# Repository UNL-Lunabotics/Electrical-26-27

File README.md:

# Electrical-26-27
Electrical's pcb projects and documentation.

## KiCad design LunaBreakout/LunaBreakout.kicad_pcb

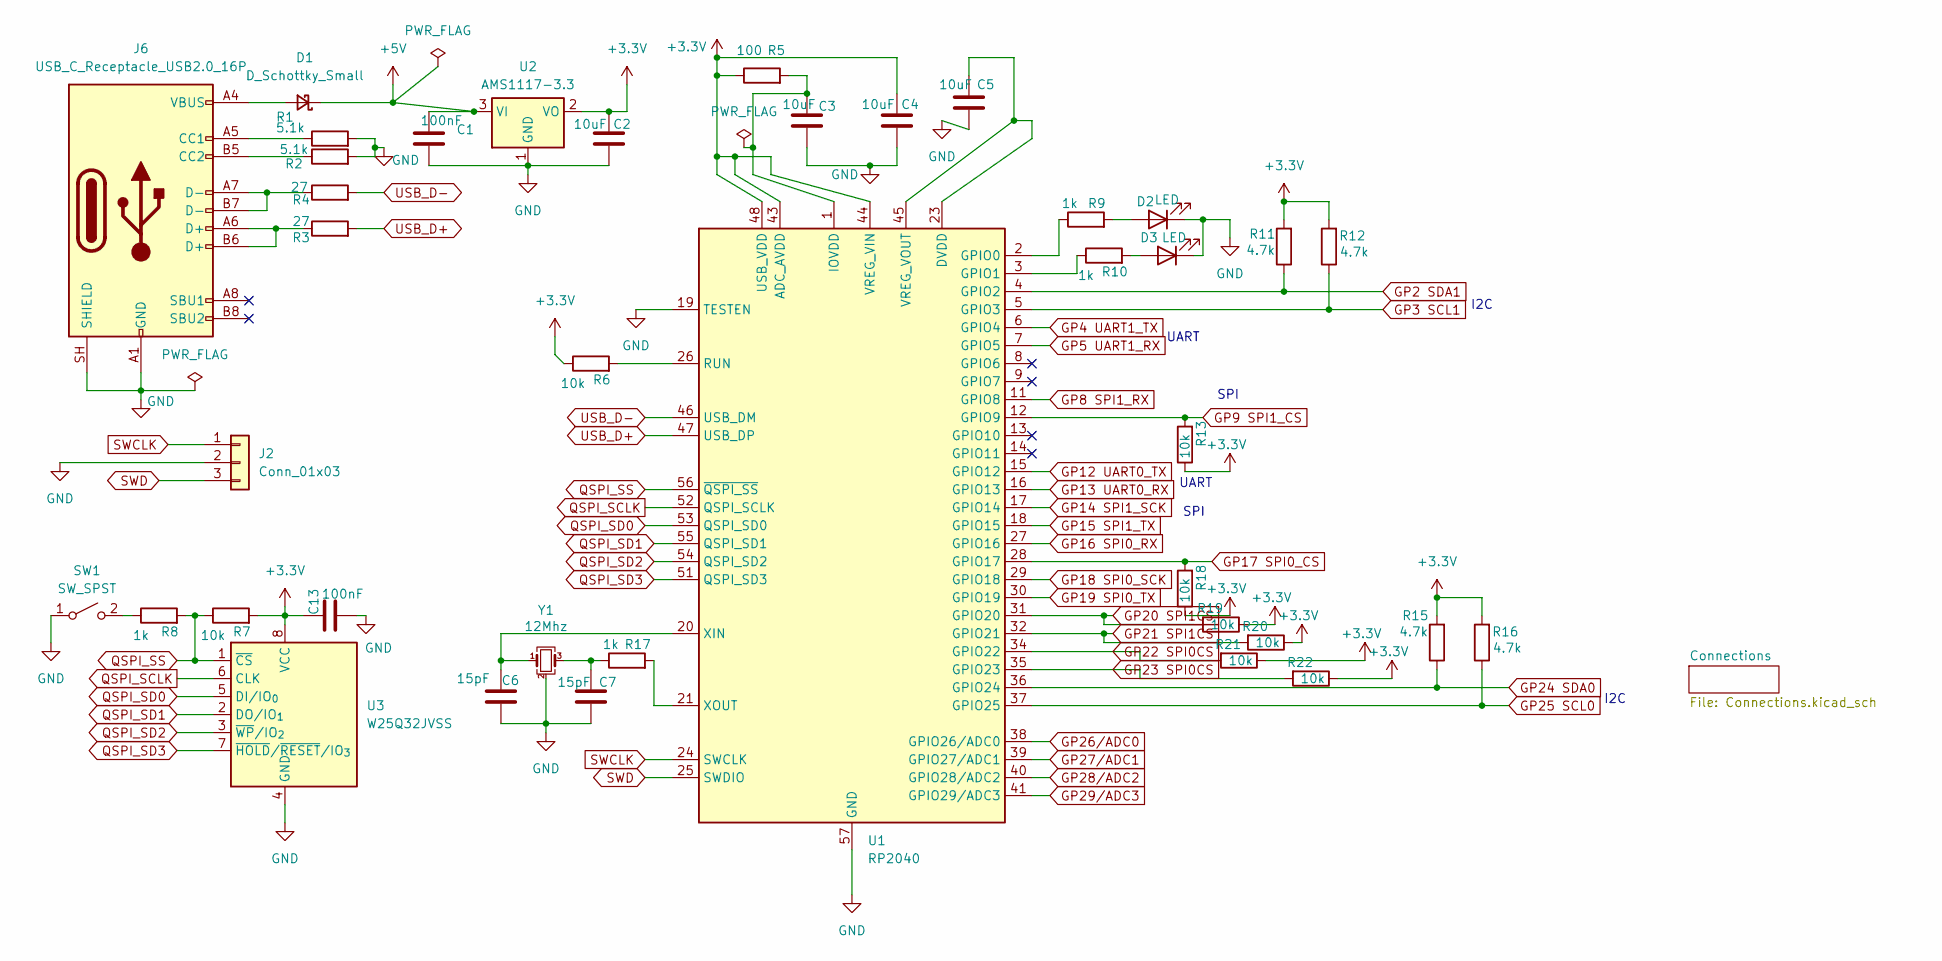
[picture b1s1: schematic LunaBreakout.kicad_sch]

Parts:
C1, C13: 100nF; C_0805_2012Metric
C2, C3, C4, C5: 10uF; C_0805_2012Metric
C6, C7: 15pF; C_0805_2012Metric
D1: D_Schottky_Small; D_SMA
D2, D3: LED; LED_0805_2012Metric
J2: Conn_01x03; JST_XH_B3B-XH-A_1x03_P2.50mm_Vertical
J6: USB_C_Receptacle_USB2.0_16P; USB_C_Receptacle_HRO_TYPE-C-31-M-12
R1, R2: 5.1k; R_0805_2012Metric
R3, R4: 27; R_0805_2012Metric
R5: 100; R_0805_2012Metric
R6, R7, R13, R18, R19, R20, R21, R22: 10k; R_0805_2012Metric
R8, R9, R10, R17: 1k; R_0805_2012Metric
R11, R12, R15, R16: 4.7k; R_0805_2012Metric
SW1: SW_SPST; SW_SPST_CK_RS282G05A3
U1: RP2040; QFN-56-1EP_7x7mm_P0.4mm_EP3.2x3.2mm
U2: AMS1117-3.3; SOT-223-3_TabPin2
U3: W25Q32JVSS; WSON-8-1EP_4x4mm_P0.8mm_EP2.2x3mm
Y1: 12Mhz; Crystal_SMD_SeikoEpson_FA238V-4Pin_3.2x2.5mm

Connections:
+3.3V: C2.1, C4.1, C13.1, R5.1, R6.1, R7.2, R11.2, R12.2, R13.1, R15.2, R16.2, R18.1, R19.1, R20.1, R21.1, R22.1, U1.43 (ADC_AVDD), U1.44 (VREG_VIN), U1.48 (USB_VDD), U2.2 (VO), U3.8 (VCC); also elsewhere on the board
+5V: C1.1, D1.1 (K), U2.3 (VI)
GND: C1.2, C2.2, C3.2, C4.2, C5.2, C6.2, C7.2, C13.2, D2.1 (K), D3.1 (K), J2.2, J6.A1 (GND), J6.A12 (GND), J6.B1 (GND), J6.B12 (GND), J6.SH (SHIELD), R1.2, R2.2, SW1.1 (A), U1.19 (TESTEN), U1.57 (GND), U2.1 (GND), U3.4 (GND), U3.9, Y1.2 (G), Y1.4 (G); also elsewhere on the board
GP2 SDA1: R11.1, U1.4 (GPIO2); also elsewhere on the board
GP3 SCL1: R12.1, U1.5 (GPIO3); also elsewhere on the board
GP4 UART1_TX: U1.6 (GPIO4); also elsewhere on the board
GP5 UART1_RX: U1.7 (GPIO5); also elsewhere on the board
GP8 SPI1_RX: U1.11 (GPIO8); also elsewhere on the board
GP9 SPI1_CS: R13.2, U1.12 (GPIO9); also elsewhere on the board
GP12 UART0_TX: U1.15 (GPIO12); also elsewhere on the board
GP13 UART0_RX: U1.16 (GPIO13); also elsewhere on the board
GP14 SPI1_SCK: U1.17 (GPIO14); also elsewhere on the board
GP15 SPI1_TX: U1.18 (GPIO15); also elsewhere on the board
GP16 SPI0_RX: U1.27 (GPIO16); also elsewhere on the board
GP17 SPI0_CS: R18.2, U1.28 (GPIO17); also elsewhere on the board
GP18 SPI0_SCK: U1.29 (GPIO18); also elsewhere on the board
GP19 SPI0_TX: U1.30 (GPIO19); also elsewhere on the board
GP20 SPI1CS: R19.2, U1.31 (GPIO20); also elsewhere on the board
GP21 SPI1CS: R20.2, U1.32 (GPIO21); also elsewhere on the board
GP22 SPI0CS: R21.2, U1.34 (GPIO22); also elsewhere on the board
GP23 SPI0CS: R22.2, U1.35 (GPIO23); also elsewhere on the board
GP24 SDA0: R15.1, U1.36 (GPIO24); also elsewhere on the board
GP25 SCL0: R16.1, U1.37 (GPIO25); also elsewhere on the board
GP26/ADC0: U1.38 (GPIO26/ADC0); also elsewhere on the board
GP27/ADC1: U1.39 (GPIO27/ADC1); also elsewhere on the board
GP28/ADC2: U1.40 (GPIO28/ADC2); also elsewhere on the board
GP29/ADC3: U1.41 (GPIO29/ADC3); also elsewhere on the board
unnamed: C3.1, R5.2, U1.1 (IOVDD), U1.10 (IOVDD), U1.22 (IOVDD), U1.33 (IOVDD), U1.42 (IOVDD), U1.49 (IOVDD)
unnamed: C7.1, R17.1, Y1.3
unnamed: D1.2 (A), J6.A4 (VBUS), J6.A9 (VBUS), J6.B4 (VBUS), J6.B9 (VBUS)
unnamed: D2.2 (A), R9.2
unnamed: D3.2 (A), R10.2
unnamed: J6.A5 (CC1), R1.1
unnamed: J6.B5 (CC2), R2.1
unnamed: J6.A6 (D+), J6.B6 (D+), R3.1
unnamed: J6.A7 (D-), J6.B7 (D-), R4.1
unnamed: R8.1, SW1.2 (B)
unnamed: R9.1, U1.2 (GPIO0)
unnamed: R10.1, U1.3 (GPIO1)
unnamed: R6.2, U1.26 (RUN)
unnamed: C5.1, U1.23 (DVDD), U1.45 (VREG_VOUT), U1.50 (DVDD)
unnamed: C6.1, U1.20 (XIN), Y1.1
unnamed: R17.2, U1.21 (XOUT)
QSPI_SCLK: U1.52 (QSPI_SCLK), U3.6 (CLK)
QSPI_SD0: U1.53 (QSPI_SD0), U3.5 (DI/IO_{0})
QSPI_SD1: U1.55 (QSPI_SD1), U3.2 (DO/IO_{1})
QSPI_SD2: U1.54 (QSPI_SD2), U3.3 (~WP/IO_{2})
QSPI_SD3: U1.51 (QSPI_SD3), U3.7 (~HOLD/~RESET/IO_{3})
QSPI_SS: R7.1, R8.2, U1.56 (~QSPI_SS), U3.1 (~CS)
SWCLK: J2.1, U1.24 (SWCLK)
SWD: J2.3, U1.25 (SWDIO)
USB_D+: R3.2, U1.47 (USB_DP)
USB_D-: R4.2, U1.46 (USB_DM)

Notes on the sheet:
I2C
SPI
UART

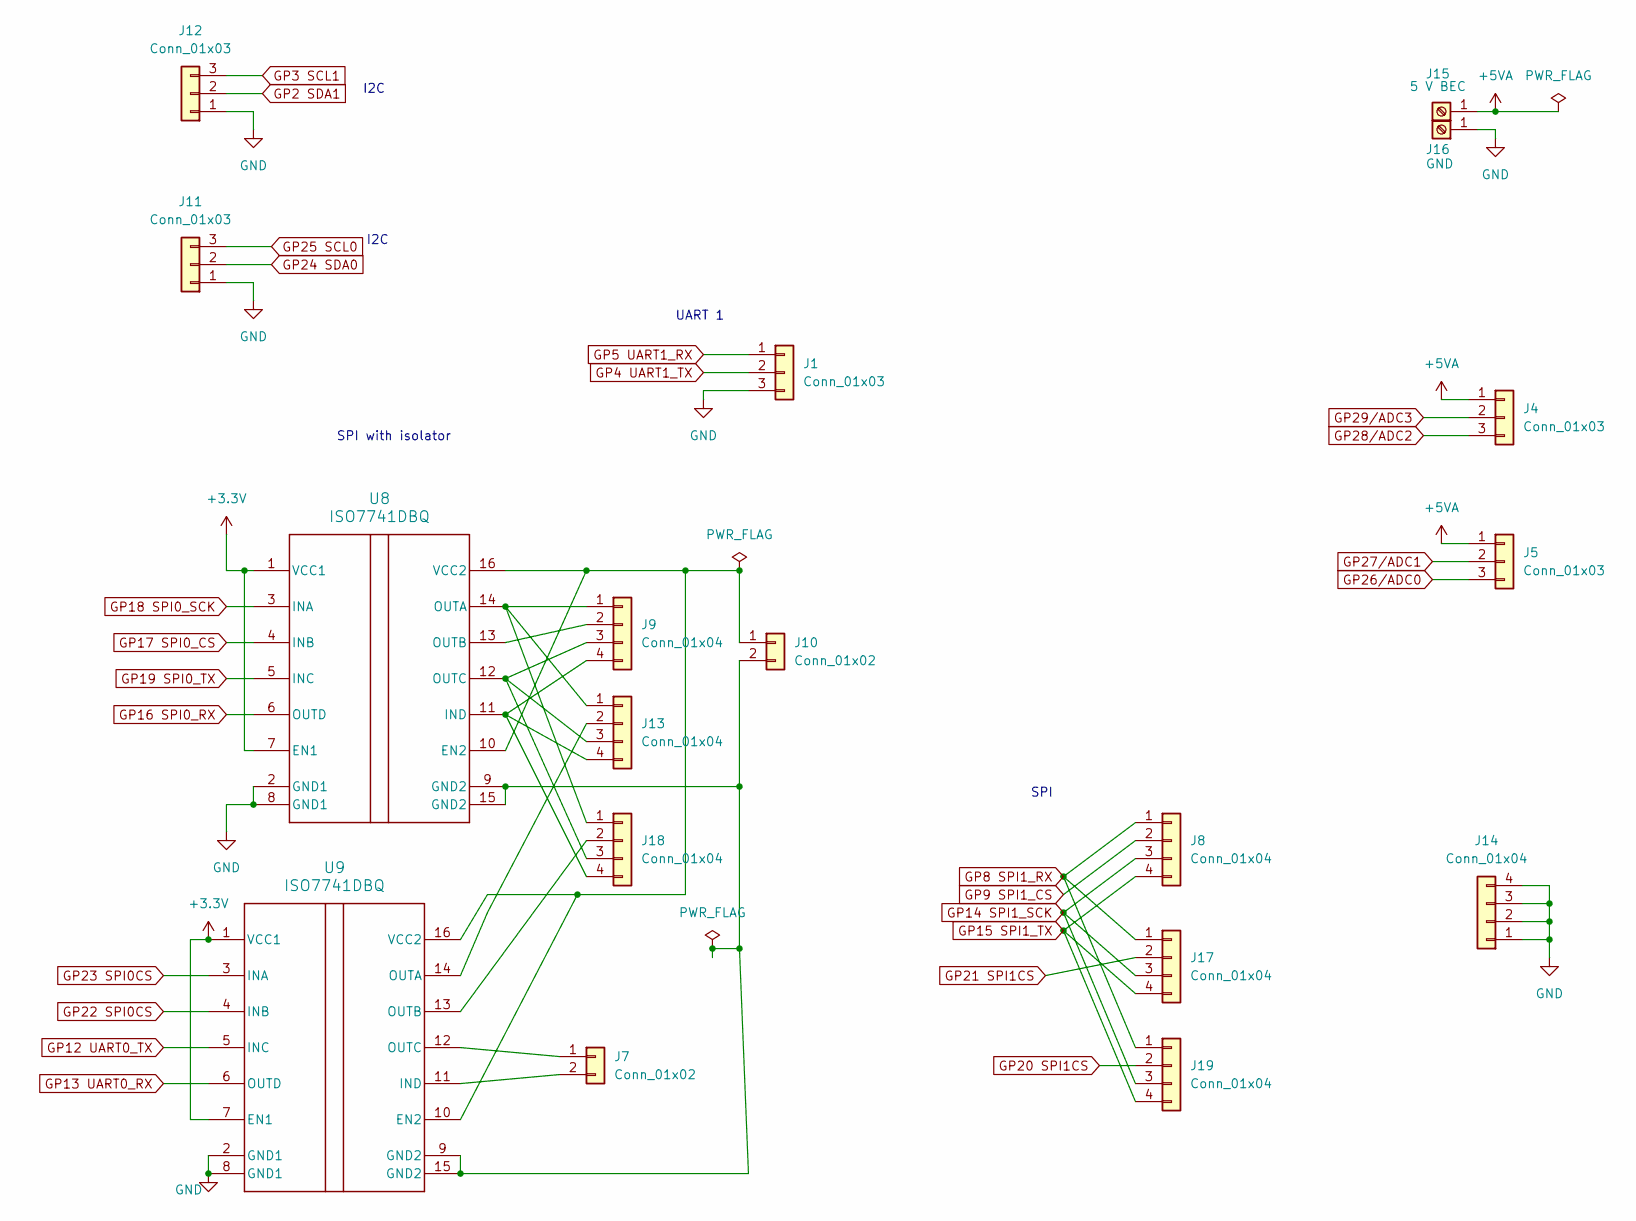
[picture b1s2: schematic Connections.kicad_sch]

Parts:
J1, J4, J5, J11, J12: Conn_01x03; JST_XH_B3B-XH-A_1x03_P2.50mm_Vertical
J7, J10: Conn_01x02; JST_XH_B2B-XH-A_1x02_P2.50mm_Vertical
J8, J9, J13, J14, J17, J18, J19: Conn_01x04; JST_XH_B4B-XH-A_1x04_P2.50mm_Vertical
J15: 5 V BEC; Amphenol_Anytek_AMT0440008DB0000G
J16: GND; Amphenol_Anytek_AMT0440008DB0000G
U8, U9: ISO7741DBQ; DBQ0016A_N

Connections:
+3.3V: U8.1 (VCC1), U8.7 (EN1), U9.1 (VCC1), U9.7 (EN1); also elsewhere on the board
+5VA: J4.1, J5.1, J15.1 (Pin_1_1)
GND: J1.3, J11.1, J12.1, J14.1, J14.2, J14.3, J14.4, J16.1 (Pin_1_1), U8.2 (GND1), U8.8 (GND1), U9.2 (GND1), U9.8 (GND1); also elsewhere on the board
GP2 SDA1: J12.2; also elsewhere on the board
GP3 SCL1: J12.3; also elsewhere on the board
GP4 UART1_TX: J1.2; also elsewhere on the board
GP5 UART1_RX: J1.1; also elsewhere on the board
GP8 SPI1_RX: J8.1, J17.1, J19.1; also elsewhere on the board
GP9 SPI1_CS: J8.2; also elsewhere on the board
GP12 UART0_TX: U9.5 (INC); also elsewhere on the board
GP13 UART0_RX: U9.6 (OUTD); also elsewhere on the board
GP14 SPI1_SCK: J8.3, J17.3, J19.3; also elsewhere on the board
GP15 SPI1_TX: J8.4, J17.4, J19.4; also elsewhere on the board
GP16 SPI0_RX: U8.6 (OUTD); also elsewhere on the board
GP17 SPI0_CS: U8.4 (INB); also elsewhere on the board
GP18 SPI0_SCK: U8.3 (INA); also elsewhere on the board
GP19 SPI0_TX: U8.5 (INC); also elsewhere on the board
GP20 SPI1CS: J19.2; also elsewhere on the board
GP21 SPI1CS: J17.2; also elsewhere on the board
GP22 SPI0CS: U9.4 (INB); also elsewhere on the board
GP23 SPI0CS: U9.3 (INA); also elsewhere on the board
GP24 SDA0: J11.2; also elsewhere on the board
GP25 SCL0: J11.3; also elsewhere on the board
GP26/ADC0: J5.3; also elsewhere on the board
GP27/ADC1: J5.2; also elsewhere on the board
GP28/ADC2: J4.3; also elsewhere on the board
GP29/ADC3: J4.2; also elsewhere on the board
unnamed: J7.1, U9.12 (OUTC)
unnamed: J7.2, U9.11 (IND)
unnamed: J9.2, U8.13 (OUTB)
unnamed: J10.1, U8.10 (EN2), U8.16 (VCC2), U9.10 (EN2), U9.16 (VCC2)
unnamed: J10.2, U8.9 (GND2), U8.15 (GND2), U9.9 (GND2), U9.15 (GND2)
unnamed: J9.1, J13.1, J18.1, U8.14 (OUTA)
unnamed: J13.2, U9.14 (OUTA)
unnamed: J9.3, J13.3, J18.3, U8.12 (OUTC)
unnamed: J9.4, J13.4, J18.4, U8.11 (IND)
unnamed: J18.2, U9.13 (OUTB)

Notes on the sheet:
SPI
SPI with isolator
I2C
UART 1

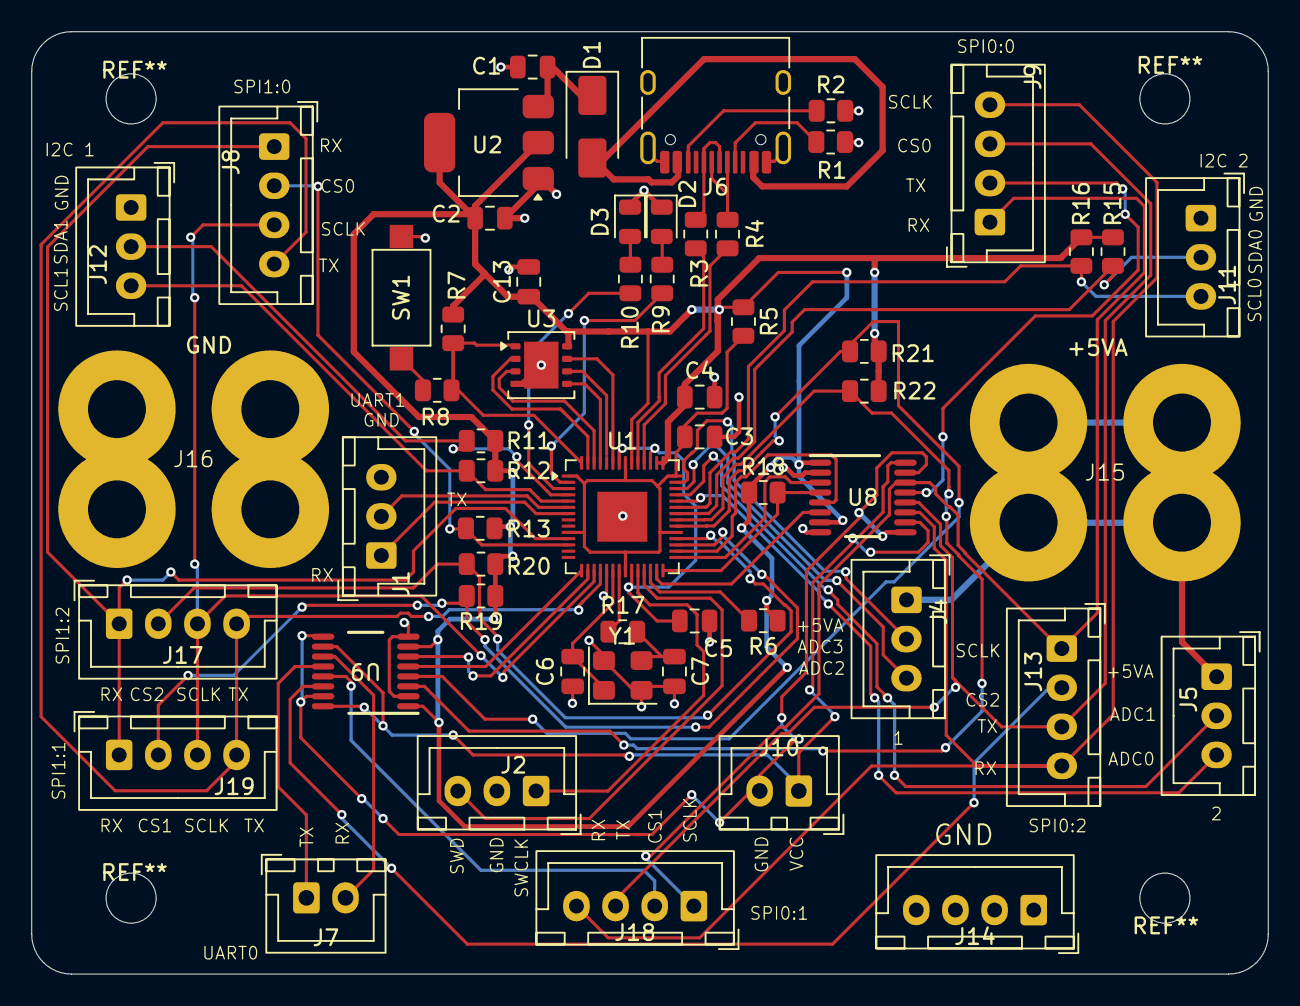
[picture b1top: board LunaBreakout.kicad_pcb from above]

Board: 2 copper layers, 79.0 x 60.2 mm, 57 parts (0 on the bottom side), 64 nets.

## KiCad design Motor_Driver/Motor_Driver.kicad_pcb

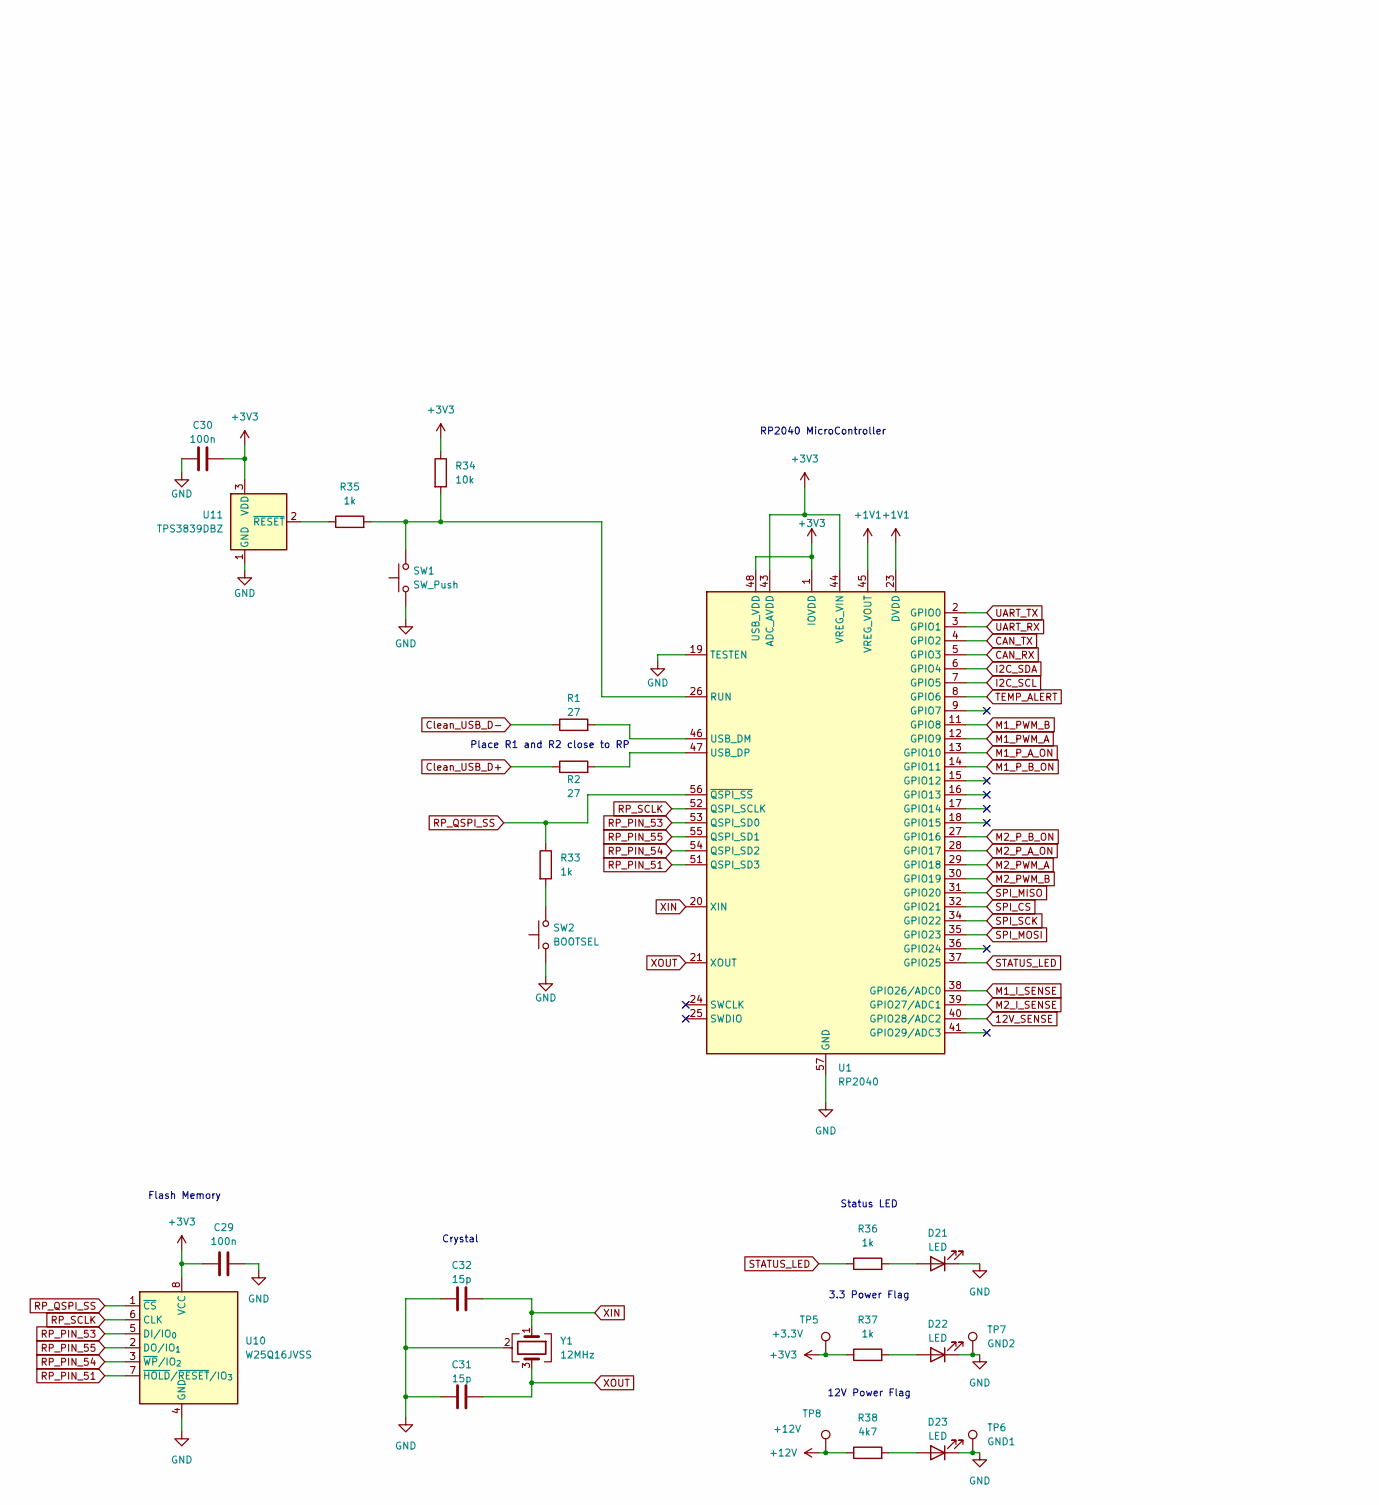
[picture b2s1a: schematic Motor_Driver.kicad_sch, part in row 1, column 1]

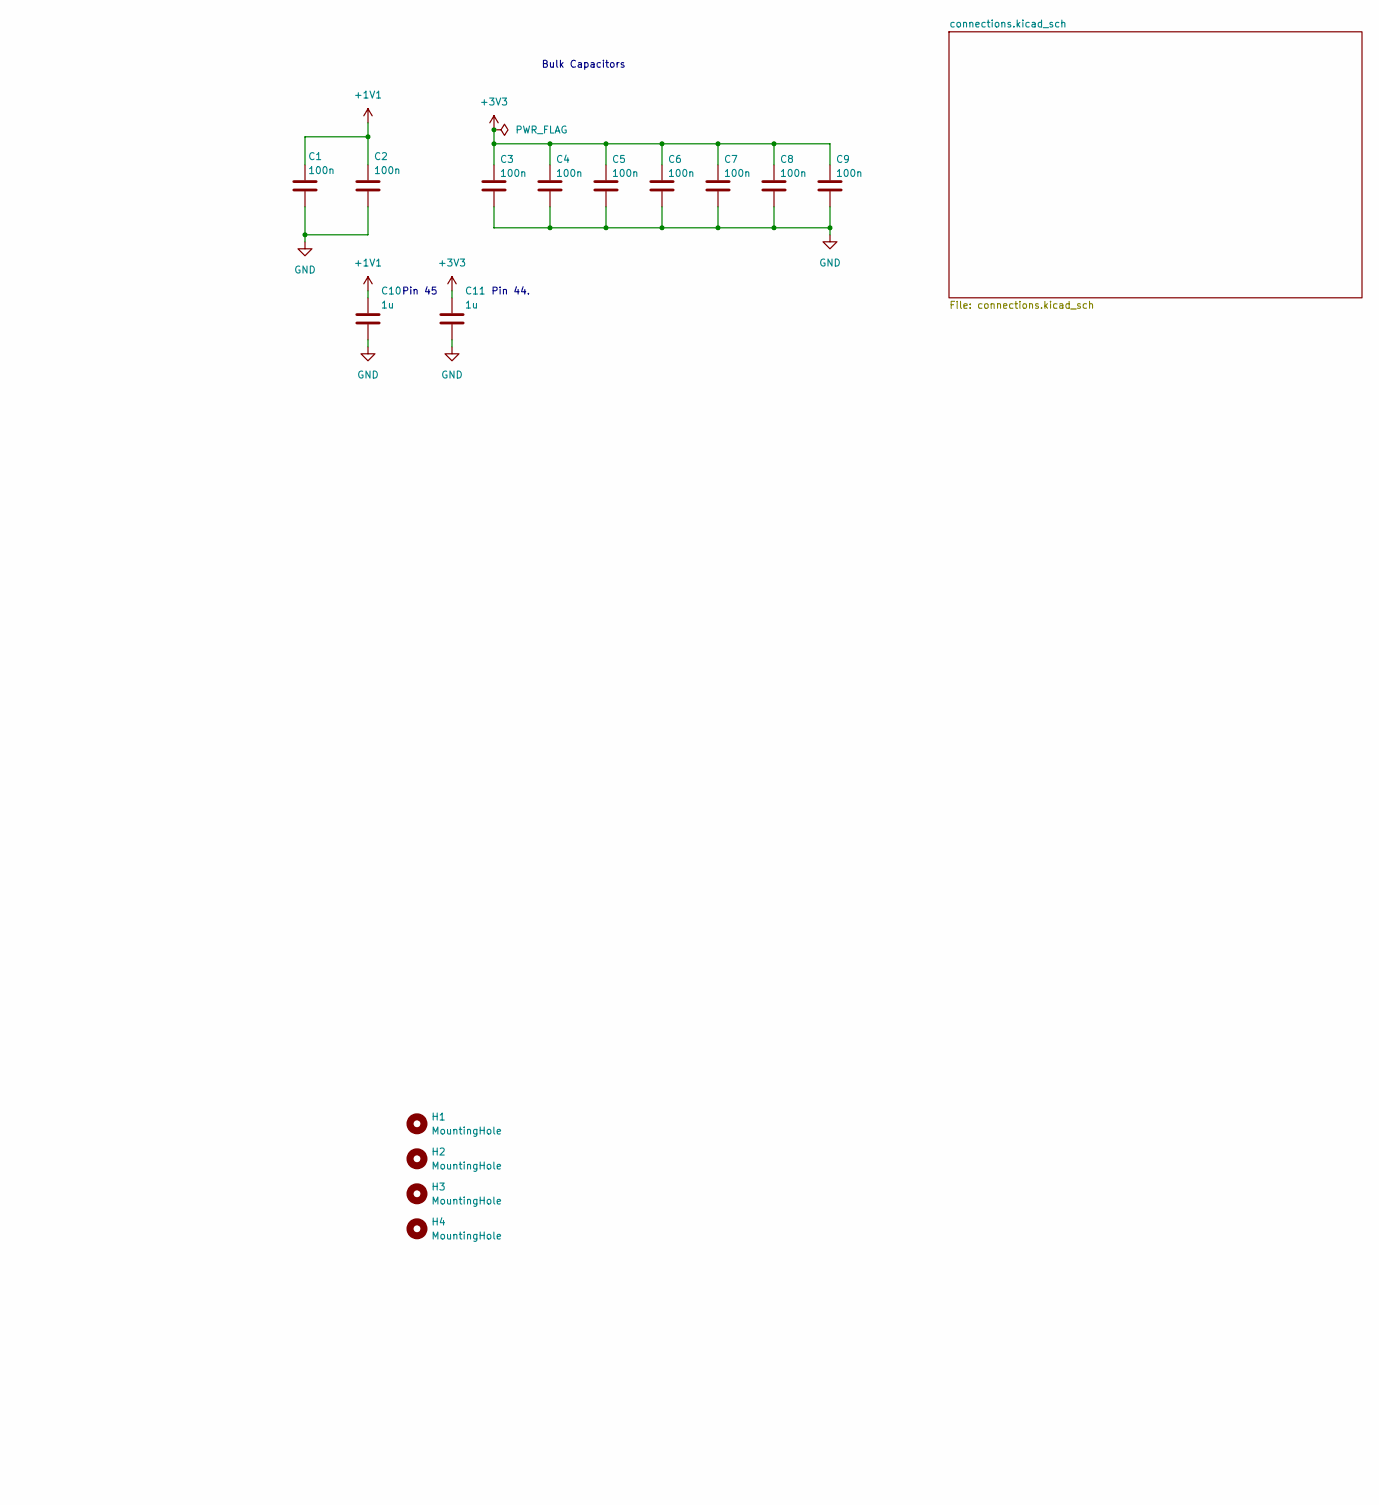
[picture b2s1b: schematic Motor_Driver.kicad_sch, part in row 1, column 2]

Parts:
C1, C2, C3, C4, C5, C6, C7, C8, C9, C29, C30: 100n; C_0805_2012Metric
C10, C11: 1u; C_0805_2012Metric
C31, C32: 15p; C_0805_2012Metric; Digikey_ID CC0805JRNPO9BN150
D21, D22, D23: LED; LED_0805_2012Metric
H1, H2, H3, H4: MountingHole; MountingHole_3.2mm_M3
R1, R2: 27; R_0805_2012Metric
R33, R35, R36, R37: 1k; R_0805_2012Metric
R34: 10k; R_0805_2012Metric
R38: 4k7; R_0805_2012Metric
SW1: SW_Push; SW_PUSH_6mm; Digikey_ID B3F-1000
SW2: BOOTSEL; SW_PUSH_6mm; Digikey_ID B3F-1000
TP5: +3.3V; TestPoint_Pad_D1.5mm
TP6: GND1; TestPoint_Pad_D1.5mm
TP7: GND2; TestPoint_Pad_D1.5mm
TP8: +12V; TestPoint_Pad_D1.5mm
U1: RP2040; QFN-56-1EP_7x7mm_P0.4mm_EP3.2x3.2mm; Digikey_ID SC0914(13)
U10: W25Q16JVSS; WSON-8-1EP_4x4mm_P0.8mm_EP2.2x3mm; Digikey_ID W25Q16JVSSIQ
U11: TPS3839DBZ; SOT-23; Digikey_ID TPS3839K33DBZR
Y1: 12MHz; Crystal_SMD_3225-4Pin_3.2x2.5mm; Digikey_ID ABM8-272-T3

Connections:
12V_SENSE: U1.40 (GPIO28/ADC2); also elsewhere on the board
+1V1: C1.1, C2.1, C10.1, U1.23 (DVDD), U1.45 (VREG_VOUT), U1.50 (DVDD)
+3V3: C3.1, C4.1, C5.1, C6.1, C7.1, C8.1, C9.1, C11.1, C29.1, C30.1, R34.1, R37.1, TP5.1 (1_1), U1.1 (IOVDD), U1.10 (IOVDD), U1.22 (IOVDD), U1.33 (IOVDD), U1.42 (IOVDD), U1.43 (ADC_AVDD), U1.44 (VREG_VIN), U1.48 (USB_VDD), U1.49 (IOVDD), U10.8 (VCC), U11.3 (VDD); also elsewhere on the board
+12V: R38.1, TP8.1 (1_1); also elsewhere on the board
CAN_RX: U1.5 (GPIO3); also elsewhere on the board
CAN_TX: U1.4 (GPIO2); also elsewhere on the board
Clean_USB_D+: R2.1; also elsewhere on the board
Clean_USB_D-: R1.1; also elsewhere on the board
GND: C1.2, C2.2, C3.2, C4.2, C5.2, C6.2, C7.2, C8.2, C9.2, C10.2, C11.2, C29.2, C30.2, C31.1, C32.1, D21.1 (K), D22.1 (K), D23.1 (K), SW1.1, SW2.1, TP6.1 (1_1), TP7.1 (1_1), U1.19 (TESTEN), U1.57 (GND), U10.4 (GND), U11.1 (GND), Y1.2 (G), Y1.4 (G); also elsewhere on the board
I2C_SCL: U1.7 (GPIO5); also elsewhere on the board
I2C_SDA: U1.6 (GPIO4); also elsewhere on the board
M1_I_SENSE: U1.38 (GPIO26/ADC0); also elsewhere on the board
M1_PWM_A: U1.12 (GPIO9); also elsewhere on the board
M1_PWM_B: U1.11 (GPIO8); also elsewhere on the board
M1_P_A_ON: U1.13 (GPIO10); also elsewhere on the board
M1_P_B_ON: U1.14 (GPIO11); also elsewhere on the board
M2_I_SENSE: U1.39 (GPIO27/ADC1); also elsewhere on the board
M2_PWM_A: U1.29 (GPIO18); also elsewhere on the board
M2_PWM_B: U1.30 (GPIO19); also elsewhere on the board
M2_P_A_ON: U1.28 (GPIO17); also elsewhere on the board
M2_P_B_ON: U1.27 (GPIO16); also elsewhere on the board
unnamed: D21.2 (A), R36.2
unnamed: D22.2 (A), R37.2
unnamed: D23.2 (A), R38.2
unnamed: R33.2, SW2.2
unnamed: R34.2, R35.2, SW1.2, U1.26 (RUN)
unnamed: R1.2, U1.46 (USB_DM)
unnamed: R2.2, U1.47 (USB_DP)
unnamed: R35.1, U11.2 (~RESET)
RP_PIN_51: U1.51 (QSPI_SD3), U10.7 (~HOLD/~RESET/IO_{3})
RP_PIN_53: U1.53 (QSPI_SD0), U10.5 (DI/IO_{0})
RP_PIN_54: U1.54 (QSPI_SD2), U10.3 (~WP/IO_{2})
RP_PIN_55: U1.55 (QSPI_SD1), U10.2 (DO/IO_{1})
RP_QSPI_SS: R33.1, U1.56 (~QSPI_SS), U10.1 (~CS)
RP_SCLK: U1.52 (QSPI_SCLK), U10.6 (CLK)
SPI_CS: U1.32 (GPIO21); also elsewhere on the board
SPI_MISO: U1.31 (GPIO20); also elsewhere on the board
SPI_MOSI: U1.35 (GPIO23); also elsewhere on the board
SPI_SCK: U1.34 (GPIO22); also elsewhere on the board
STATUS_LED: R36.1, U1.37 (GPIO25)
TEMP_ALERT: U1.8 (GPIO6); also elsewhere on the board
UART_RX: U1.3 (GPIO1); also elsewhere on the board
UART_TX: U1.2 (GPIO0); also elsewhere on the board
XIN: C32.2, U1.20 (XIN), Y1.1
XOUT: C31.2, U1.21 (XOUT), Y1.3

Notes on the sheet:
Pin 44.
12V Power Flag
Pin 45
Bulk Capacitors
Status LED
3.3 Power Flag
Flash Memory
Crystal
RP2040 MicroController
Place R1 and R2 close to RP

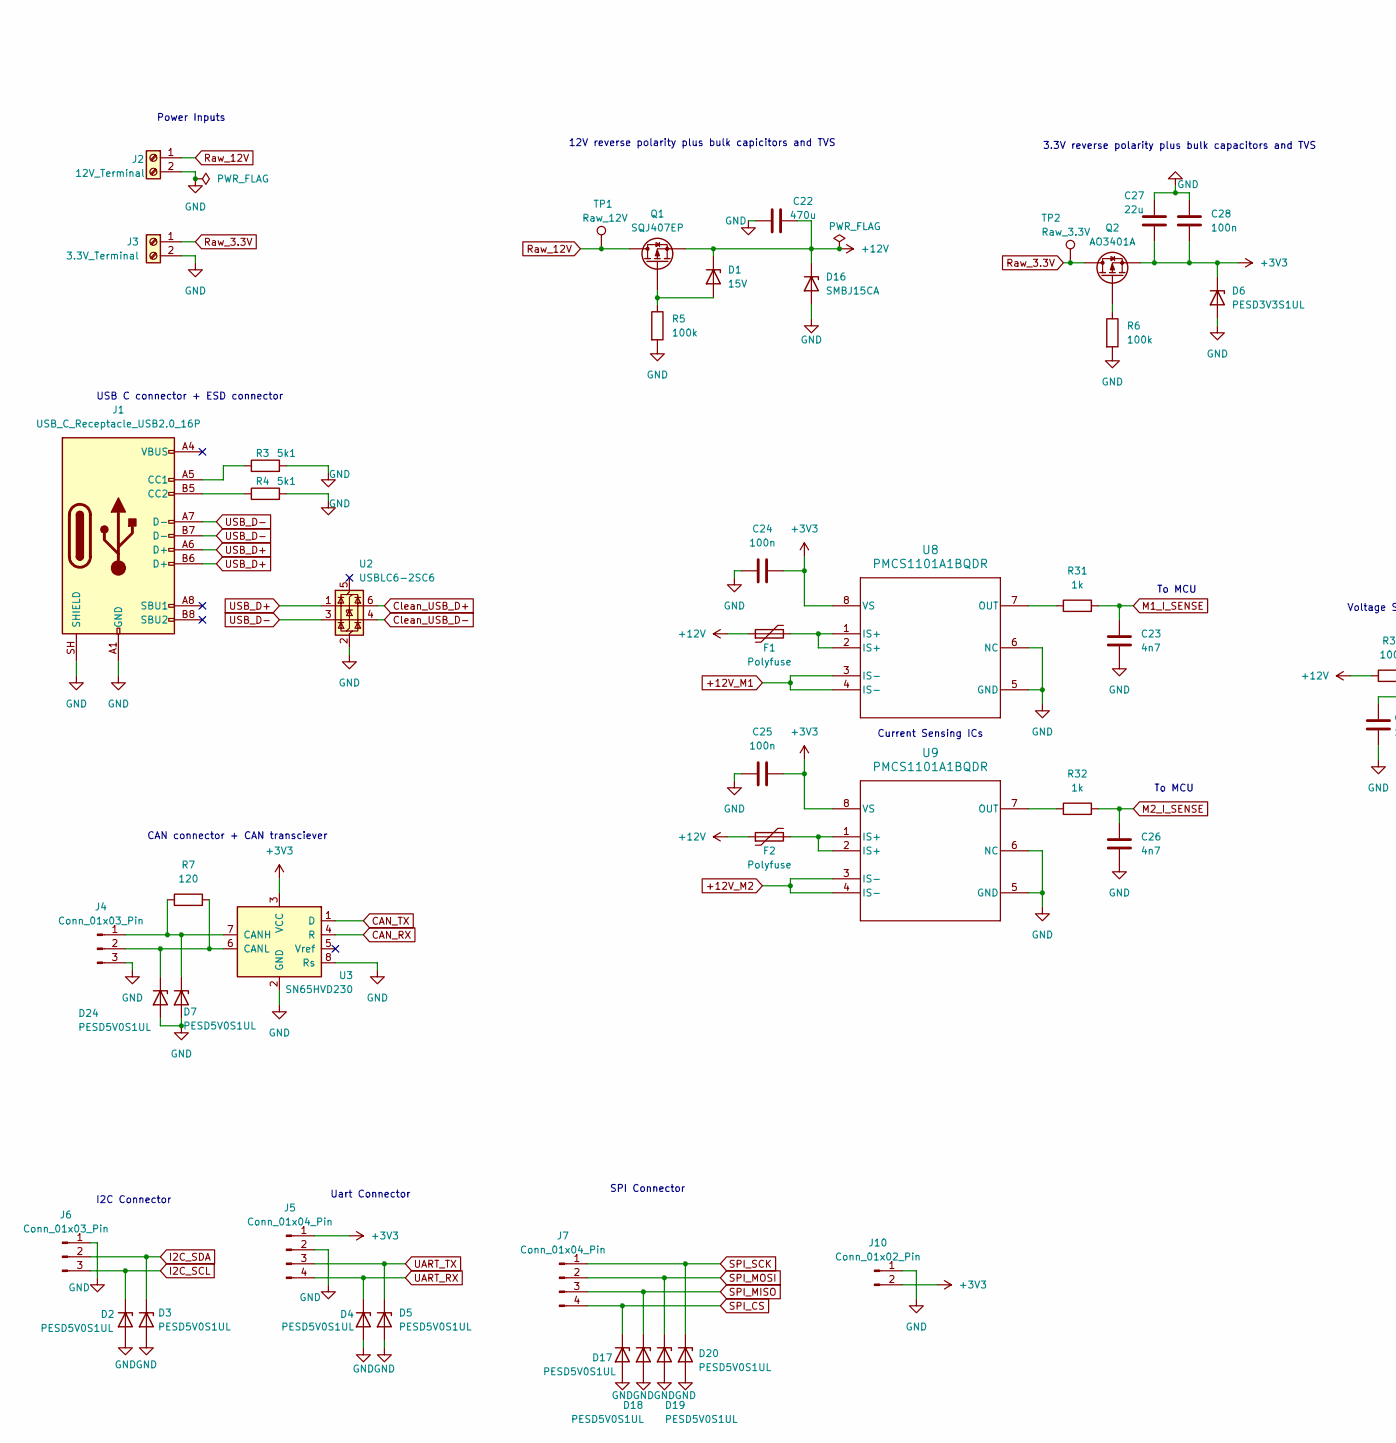
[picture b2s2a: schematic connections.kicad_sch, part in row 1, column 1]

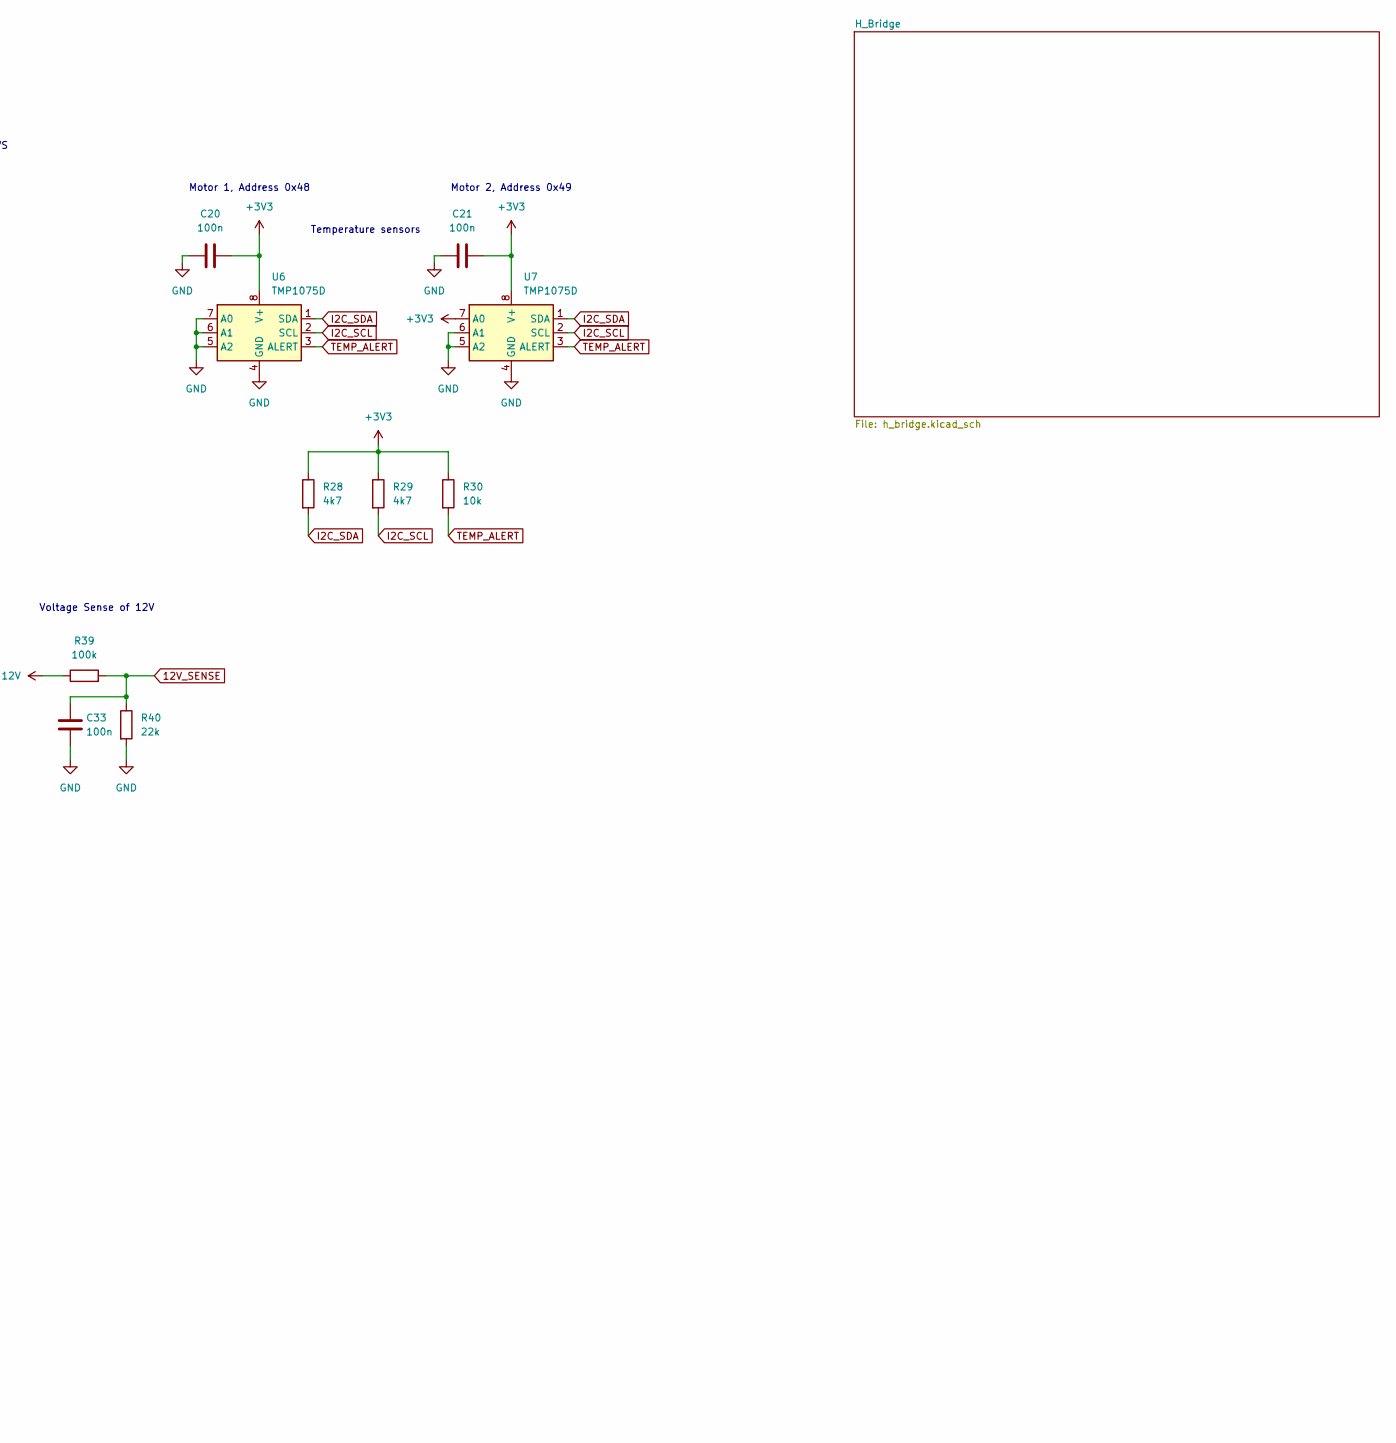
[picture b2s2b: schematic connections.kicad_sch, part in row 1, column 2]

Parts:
C20, C21, C24, C25, C28, C33: 100n; C_0805_2012Metric
C22: 470u; CP_Elec_10x10.5; Digikey_ID CVH-1E471MH10-R
C23, C26: 4n7; C_0805_2012Metric
C27: 22u; C_0805_2012Metric; Digikey_ID CL21X226MRQNNNE
D1: 15V; D_SOD-123; Digikey_ID MMSZ5245B-TP
D2, D3, D4, D5, D7, D17, D18, D19, D20, D24: PESD5V0S1UL; D_SOD-882; Digikey_ID PESD5V0S1ULSYL
D6: PESD3V3S1UL; D_SOD-882; Digikey_ID PESD3V3S1ULSYL
D16: SMBJ15CA; D_SMB; Digikey_ID SMBJ15CA-E3/52
F1, F2: Polyfuse; Fuse_Mount
J1: USB_C_Receptacle_USB2.0_16P; USB_C_Receptacle_GCT_USB4105-xx-A_16P_TopMnt_Horizontal; Digikey_ID USB4105-GF-A-120
J2: 12V_Terminal; TerminalBlock_MaiXu_MX126-5.0-02P_1x02_P5.00mm; Digikey_ID 1729128
J3: 3.3V_Terminal; TerminalBlock_MaiXu_MX126-5.0-02P_1x02_P5.00mm; Digikey_ID 1729128
J4, J6: Conn_01x03_Pin; JST_XH_B3B-XH-A_1x03_P2.50mm_Vertical; Digikey_ID B3B-XH-A
J5, J7: Conn_01x04_Pin; JST_XH_B4B-XH-A_1x04_P2.50mm_Vertical; Digikey_ID B4B-XH-A
J10: Conn_01x02_Pin; JST_XH_B2B-XH-A_1x02_P2.50mm_Vertical; Digikey_ID B2B-XH-A
Q1: SQJ407EP; PowerPAK_SO-8_Single_SGD; Digikey_ID SQJ407EP-T1_GE3
Q2: AO3401A; SOT-23_GSD; Digikey_ID AO3401A
R3, R4: 5k1; R_0805_2012Metric
R5, R6, R39: 100k; R_0805_2012Metric
R7: 120; R_0805_2012Metric; Digikey_ID RC0805FR-07120RL
R28, R29: 4k7; R_0805_2012Metric
R30: 10k; R_0805_2012Metric
R31, R32: 1k; R_0805_2012Metric
R40: 22k; R_0805_2012Metric; Digikey_ID AC0805FR-0722K1L
TP1: Raw_12V; TestPoint_Pad_D1.5mm
TP2: Raw_3.3V; TestPoint_Pad_D1.5mm
U2: USBLC6-2SC6; SOT-23-6; Digikey_ID USBLC6-2SC6
U3: SN65HVD230; SOIC-8_3.9x4.9mm_P1.27mm; Digikey_ID SN65HVD230DR
U6, U7: TMP1075D; SO-8_3.9x4.9mm_P1.27mm; Digikey_ID TMP1075DR
U8, U9: PMCS1101A1BQDR; D0008A_N; Digikey_ID TMCS1101A1BQDR

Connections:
12V_SENSE: C33.1, R39.2, R40.1; also elsewhere on the board
+3V3: C20.2, C21.2, C24.2, C25.2, C27.2, C28.2, D6.1 (K), J5.1, J10.2, Q2.S, R28.1, R29.1, R30.1, U3.3 (VCC), U6.8 (V+), U7.7 (A0), U7.8 (V+), U8.8 (VS), U9.8 (VS); also elsewhere on the board
+12V: C22.2, D1.1 (K), D16.1 (K), F1.1, F2.1, Q1.S, R39.1; also elsewhere on the board
+12V_M1: U8.3 (IS-), U8.4 (IS-); also elsewhere on the board
+12V_M2: U9.3 (IS-), U9.4 (IS-); also elsewhere on the board
CAN_RX: U3.4 (R); also elsewhere on the board
CAN_TX: U3.1 (D); also elsewhere on the board
Clean_USB_D+: U2.6 (I/O1); also elsewhere on the board
Clean_USB_D-: U2.4 (I/O2); also elsewhere on the board
GND: C20.1, C21.1, C22.1, C23.2, C24.1, C25.1, C26.2, C27.1, C28.1, C33.2, D2.2 (A), D3.2 (A), D4.2 (A), D5.2 (A), D6.2 (A), D7.2 (A), D16.2 (A), D17.2 (A), D18.2 (A), D19.2 (A), D20.2 (A), D24.2 (A), J1.A1 (GND), J1.A12 (GND), J1.B1 (GND), J1.B12 (GND), J1.SH (SHIELD), J2.2, J3.2, J4.3, J5.2, J6.1, J10.1, R3.2, R4.2, R5.2, R6.2, R40.2, U2.2 (GND), U3.2 (GND), U3.8 (Rs), U6.4 (GND), U6.5 (A2), U6.6 (A1), U6.7 (A0), U7.4 (GND), U7.5 (A2), U7.6 (A1), U8.5 (GND), U8.6 (NC), U9.5 (GND), U9.6 (NC); also elsewhere on the board
I2C_SCL: D2.1 (K), J6.3, R29.2, U6.2 (SCL), U7.2 (SCL); also elsewhere on the board
I2C_SDA: D3.1 (K), J6.2, R28.2, U6.1 (SDA), U7.1 (SDA); also elsewhere on the board
M1_I_SENSE: C23.1, R31.2; also elsewhere on the board
M2_I_SENSE: C26.1, R32.2; also elsewhere on the board
unnamed: D1.2 (A), Q1.G, R5.1
unnamed: D7.1 (K), J4.1, R7.1, U3.7 (CANH)
unnamed: D24.1 (K), J4.2, R7.2, U3.6 (CANL)
unnamed: F1.2, U8.1 (IS+), U8.2 (IS+)
unnamed: F2.2, U9.1 (IS+), U9.2 (IS+)
unnamed: J1.A5 (CC1), R3.1
unnamed: J1.B5 (CC2), R4.1
unnamed: Q2.G, R6.1
unnamed: R31.1, U8.7 (OUT)
unnamed: R32.1, U9.7 (OUT)
Raw_3.3V: J3.1, Q2.D, TP2.1 (1_1)
Raw_12V: J2.1, Q1.D, TP1.1 (1_1)
SPI_CS: D17.1 (K), J7.4; also elsewhere on the board
SPI_MISO: D18.1 (K), J7.3; also elsewhere on the board
SPI_MOSI: D19.1 (K), J7.2; also elsewhere on the board
SPI_SCK: D20.1 (K), J7.1; also elsewhere on the board
TEMP_ALERT: R30.2, U6.3 (ALERT), U7.3 (ALERT); also elsewhere on the board
UART_RX: D4.1 (K), J5.4; also elsewhere on the board
UART_TX: D5.1 (K), J5.3; also elsewhere on the board
USB_D+: J1.A6 (D+), J1.B6 (D+), U2.1 (I/O1)
USB_D-: J1.A7 (D-), J1.B7 (D-), U2.3 (I/O2)

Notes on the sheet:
Temperature sensors
Motor 1, Address 0x48
I2C Connector
To MCU
USB C connector + ESD connector
3.3V reverse polarity plus bulk capacitors and TVS
12V reverse polarity plus bulk capicitors and TVS
Current Sensing ICs
Motor 2, Address 0x49
CAN connector + CAN transciever
Power Inputs
Voltage Sense of 12V
SPI Connector
Uart Connector
